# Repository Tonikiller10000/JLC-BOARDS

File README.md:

# JLC1
### Description:
This is the first set of boards ordered for personal projects and it contains this modules:  
- [Sensor Bar (used for the finefollower)](https://github.com/Tonikiller10000/ITR8307-TR8_SensorBar)
- [FE1.1s USB HUB](https://github.com/Tonikiller10000/FE1.1S_USBHUB)
- [CH340G FTDI Programmer](https://github.com/Tonikiller10000/CH340G-FTDI-PROGRAMER)
- [ATmega32U4 microcontroller](https://github.com/Tonikiller10000/ATmega32U4)
- [ATmega16U2 microcontroller](https://github.com/Tonikiller10000/ATmega16U2)
- [AT90USB162 microcontroller](https://github.com/Tonikiller10000/AT90USB162)
- [EEPROM Programmer](https://github.com/Tonikiller10000/EEPROM_PROGRAMER)
- other side testing boards
<table>
  <tr>
    <td></td>  
    <td></td>  
    <td></td>
    <td></td>
  </tr>      
</table>

# JLC2
### Description:
It has 4 layers and it contains:  
- [Keystroke Injection Tool](https://github.com/Tonikiller10000/KeystrokeInjectionTool)
- [USB Mass Storage Device](https://github.com/Tonikiller10000/USB-MassStorageDevice)
- testing board for some charging IC\`s
<table>
  <tr>
    <td></td>  
    <td></td>  
    <td></td>
    <td></td>
  </tr>      
</table>

# JLC3
### Description:
This is the third set of boards ordered for personal projects and contains:  
- [LineFollower_V4.0](https://github.com/Tonikiller10000/LineFollower)
- [EEPROM Programmer_V2.0](https://github.com/Tonikiller10000/EEPROM_PROGRAMER)
- [8BitProcessor_DisplayRegister](https://github.com/Tonikiller10000/8BitProcessor/tree/main/DisplayRegister)
- [8BitProcessor_ClkModule](https://github.com/Tonikiller10000/8BitProcessor/tree/main/ClkPulseGenerator)
<table>
  <tr>
    <td></td>  
    <td></td>  
    <td></td>
    <td></td>
  </tr>      
</table>

# JLC4
# JLC4_RoboChalangeBoards
This is the forth order of boards from JLC PCB. It has all the boards for the competitions robots.
It contains:
- 1x [LineFollower V5.0](https://github.com/Tonikiller10000/LineFollower)
- 1x [RoboSumo V1.0](https://github.com/Tonikiller10000/RoboSumo)
- 2x [Motor driverss with Voltage Boost up Converters](https://github.com/Tonikiller10000/MotorDriver_1)
- 2x [Motor driverss without Voltage Boost up Converters](https://github.com/Tonikiller10000/MotorDriver_1)
- 2x [LiPo battery charger](https://github.com/Tonikiller10000/LiPo_BatteryCharger)
- 2x [VL53L0x Distance sensor](https://github.com/Tonikiller10000/VL53L0x_DistanceSensor)
- 1x [FTDI programmer V2.0](https://github.com/Tonikiller10000/CH340G-FTDI-PROGRAMER)
- 1x [FTDI programmer V2.1](https://github.com/Tonikiller10000/CH340G-FTDI-PROGRAMER)
- 1x [sensor bar](https://github.com/Tonikiller10000/ITR8307-TR8_SensorBar)
<table>
  <tr>
    <td></td>  
    <td></td>  
    <td></td>
  </tr>      
</table>

# JLC5 - 2 layers
### It contains:
- [EEPROM Programmer](https://github.com/Tonikiller10000/EEPROM_PROGRAMER);
- [TPA3128D2_AudioAmplifier](https://github.com/Tonikiller10000/TPA3128D2_AudioAmplifier);
- [SD card reader](https://github.com/Tonikiller10000/USB-MicroSD_CardReader);
- [Keystroke injection tool](https://github.com/Tonikiller10000/KeystrokeInjectionTool);
- [Ultrasonic phased array](https://github.com/Tonikiller10000/UltrasonicPhasedArray);
- Mems microphones test boards;
- other testing boards.

### The board:
<table>
  <tr>
    <td></td>  
    <td></td>  
    <td></td>  
  </tr>      
</table>

# JLC6 - PCBcoils

### description:
The board contains some pcb coils for teasting and research purposes.

### The board:
<table>
  <tr>
    <td></td>  
    <td></td>  
    <td></td>  
  </tr>      
</table>

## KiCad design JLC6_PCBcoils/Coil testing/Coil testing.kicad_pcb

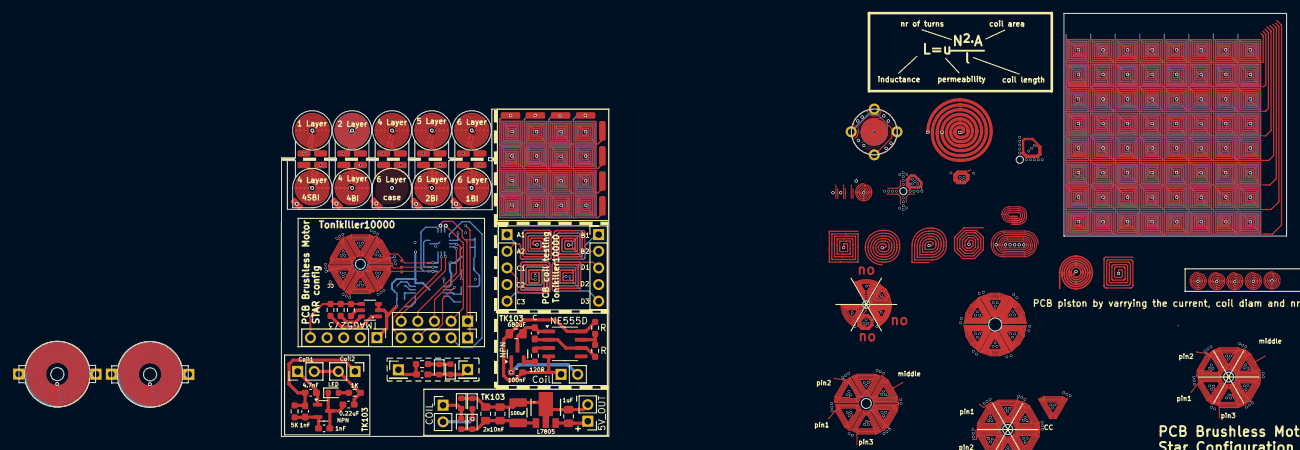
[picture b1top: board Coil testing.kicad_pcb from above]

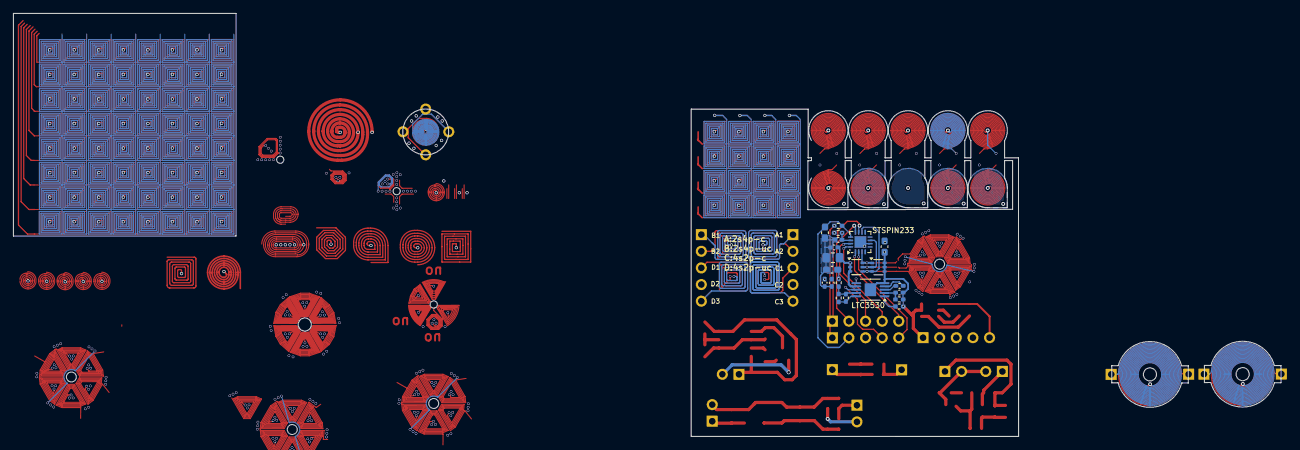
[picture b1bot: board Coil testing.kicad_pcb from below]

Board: 8 copper layers, 193.6 x 64.6 mm, 54 parts (21 on the bottom side), 34 nets.

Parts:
C1: 100uF; C_0805_2012Metric_Pad1.18x1.45mm_HandSolder
C2, C7: 10uF; C_0603_1608Metric_Pad1.08x0.95mm_HandSolder
C3: 100nF; C_0402_1005Metric_Pad0.74x0.62mm_HandSolder
C4, C5, C6: c; C_0402_1005Metric_Pad0.74x0.62mm_HandSolder
C8: 1uF; C_0402_1005Metric_Pad0.74x0.62mm_HandSolder
C9: 1nF; C_0402_1005Metric_Pad0.74x0.62mm_HandSolder
C10: 10nF; C_0603_1608Metric_Pad1.08x0.95mm_HandSolder
C11: c; C_0603_1608Metric_Pad1.08x0.95mm_HandSolder
C12: 680uF; C_0805_2012Metric_Pad1.18x1.45mm_HandSolder
C13, C14: 100nF; C_0603_1608Metric_Pad1.08x0.95mm_HandSolder
C15, C20: 10nF; C_0805_2012Metric_Pad1.18x1.45mm_HandSolder
C16, C17: 1nF; C_0603_1608Metric_Pad1.08x0.95mm_HandSolder
C18: 4.7nF; C_0603_1608Metric_Pad1.08x0.95mm_HandSolder
C19: 0.22uF; C_0603_1608Metric_Pad1.08x0.95mm_HandSolder
C21: 100uF; C_1210_3225Metric_Pad1.33x2.70mm_HandSolder
C22: 1uF; C_0805_2012Metric_Pad1.18x1.45mm_HandSolder
D1, D2: MMBD4448HTW; SOT-363_SC-70-6
D3, D4, D8: LED; D_0603_1608Metric
D6, D7, D9, D10: D; D_0603_1608Metric
L4: 4.7uH; C_0402_1005Metric_Pad0.74x0.62mm_HandSolder
Q1, Q3: NPN; SOT-23
R1: 33.2K; R_0402_1005Metric_Pad0.72x0.64mm_HandSolder
R2: 390K; R_0402_1005Metric_Pad0.72x0.64mm_HandSolder
R3: 120K; R_0402_1005Metric_Pad0.72x0.64mm_HandSolder
R4: R; R_0402_1005Metric_Pad0.72x0.64mm_HandSolder
R5, R6: 20K; R_0402_1005Metric_Pad0.72x0.64mm_HandSolder
R7, R8: R; R_0603_1608Metric_Pad0.98x0.95mm_HandSolder
R9: 120R; R_0603_1608Metric_Pad0.98x0.95mm_HandSolder
R10: 5R; R_0603_1608Metric_Pad0.98x0.95mm_HandSolder
R12, R15, R16: 10K; R_0603_1608Metric_Pad0.98x0.95mm_HandSolder
R13: 1K; R_0603_1608Metric_Pad0.98x0.95mm_HandSolder
R14: 5K; R_0603_1608Metric_Pad0.98x0.95mm_HandSolder
U1: LTC3530; MSOP-10-1EP_3x3mm_P0.5mm_EP1.73x1.98mm
U2: STSPIN233; VQFN-16-1EP_3x3mm_P0.5mm_EP1.8x1.8mm
U3: NE555D; SOIC-8_3.9x4.9mm_P1.27mm
U4: L7805; PK(R-PSSO-F3)
U5: TMAG5273; DBV0006A

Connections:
3.3V: C12.1, C13.1, R8.2, R12.2, R15.2, R16.2, U3.4 (R), U3.8 (VCC), U5.4 (VCC)
+5V: C6.1, C7.1, C8.1, C22.1, R2.2, R5.2, U1.6 (Vout), U2.5 (VS), U4.3 (OUT)
+9V: C19.1, R13.2
FAULT: C10.1, R6.1, U2.13 (EN/FAULT)
GND: C1.2, C2.2, C3.2, C4.2, C6.2, C7.2, C8.2, C9.2, C10.2, C11.2, C12.2, C15.2, C17.2, C19.2, C20.2, C21.2, C22.2, D2.4 (K), D2.5 (K), D2.6 (K), D6.1 (K), D7.1 (K), D8.1 (K), Q1.3 (E), Q3.3 (E), R1.1, R4.1, U1.5 (GND), U2.6 (GND), U2.17 (GND), U3.1 (GND), U4.2 (GND), U5.2 (GND), U5.3 (TEST)
unnamed: C14.1, R10.2
unnamed: C16.1, C18.1, R14.2
unnamed: D1.6 (K), D2.1 (A), U2.3 (OUTU)
unnamed: D1.5 (K), D2.2 (A), U2.7 (OUTV)
unnamed: D1.4 (K), D2.3 (A), U2.10 (OUTW)
unnamed: C14.2, D3.2 (A), D4.1 (K)
unnamed: D3.1 (K), D4.2 (A), R10.1
unnamed: D7.2 (A), D9.1 (K)
unnamed: D8.2 (A), R13.1
unnamed: C15.1, C20.1, C21.1, D9.2 (A), D10.2 (A), U4.1 (IN)
unnamed: D6.2 (A), D10.1 (K)
unnamed: R16.1, U5.5 (~INT)
unnamed: R15.1, U5.6 (SDA)
unnamed: R12.1, U5.1 (SCL)
unnamed: Q1.2 (B), R9.1
unnamed: C13.2, Q1.1 (C)
unnamed: C16.2, C17.1, Q3.2 (B), R14.1
unnamed: C18.2, Q3.1 (C)
unnamed: C4.1, R4.2, U1.2 (BURST)
unnamed: C5.1, R2.1, R3.2, U1.9 (FB)
unnamed: R1.2, U1.1 (RT)
unnamed: L4.2, U1.3 (SW1)
unnamed: L4.1, U1.4 (SW2)
unnamed: C5.2, R3.1, U1.10 (Vc)
unnamed: R7.2, R8.1, U3.7 (DIS)
unnamed: R9.2, U3.3 (Q)
unnamed: C11.1, R7.1, U3.2 (TR), U3.6 (THR)
STBY: C9.1, R5.1, U2.14 (STBY/RESET)
V_Mot<5V: C1.1, C2.1, C3.1, D1.1 (A), D1.2 (A), D1.3 (A), U1.7 (Vin)

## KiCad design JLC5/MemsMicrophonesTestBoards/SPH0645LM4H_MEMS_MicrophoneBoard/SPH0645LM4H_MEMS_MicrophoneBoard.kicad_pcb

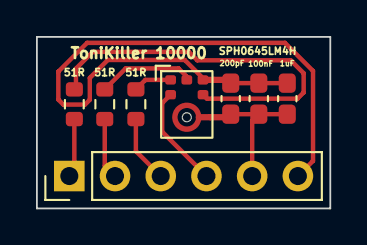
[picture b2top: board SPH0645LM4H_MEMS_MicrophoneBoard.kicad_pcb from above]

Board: 2 copper layers, 16.3 x 9.5 mm, 8 parts (0 on the bottom side), 3 nets.

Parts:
C1: 1uF; C_0603_1608Metric_Pad1.08x0.95mm_HandSolder
C2: 200pF; C_0603_1608Metric_Pad1.08x0.95mm_HandSolder
C3: 100nF; C_0603_1608Metric_Pad1.08x0.95mm_HandSolder
J1: Conn_01x06_Pin; PinHeader_1x06_P2.54mm_Vertical
MK1: SPH0645LM4H; Knowles_SPH0645LM4H-6_3.5x2.65mm
R1, R2, R3: 51R; R_0603_1608Metric

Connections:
+3V3: C1.2, C2.2, C3.2, J1.6, MK1.5 (VDD)
GND: C1.1, C2.1, C3.1, J1.5, MK1.3 (GND)
M_SEL: J1.4, MK1.2 (SEL)

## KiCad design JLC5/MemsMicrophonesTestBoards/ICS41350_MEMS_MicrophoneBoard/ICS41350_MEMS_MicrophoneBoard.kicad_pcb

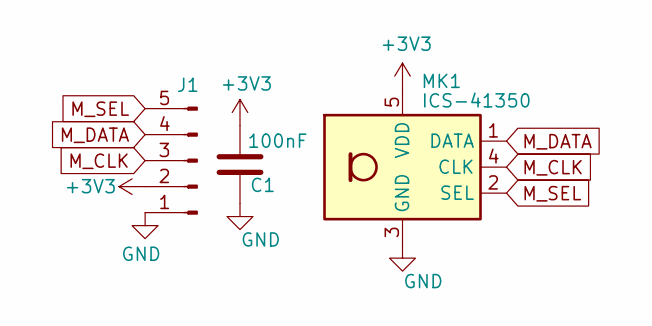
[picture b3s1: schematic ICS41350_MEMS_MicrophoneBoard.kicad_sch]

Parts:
C1: 100nF
J1: Conn_01x05_Pin
MK1: ICS-41350; Knowles_SPH0645LM4H-6_3.5x2.65mm

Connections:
+3V3: C1.2, J1.2, MK1.5 (VDD)
GND: C1.1, J1.1, MK1.3 (GND)
M_CLK: J1.3, MK1.4 (CLK)
M_DATA: J1.4, MK1.1 (DATA)
M_SEL: J1.5, MK1.2 (SEL)

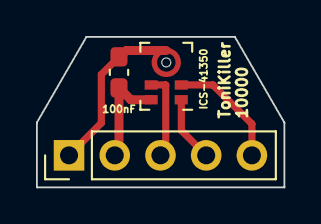
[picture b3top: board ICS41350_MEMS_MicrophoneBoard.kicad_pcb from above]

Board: 2 copper layers, 13.8 x 8.4 mm, 3 parts (0 on the bottom side), 5 nets.

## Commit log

2024-06-29 init
